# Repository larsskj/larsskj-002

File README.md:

An Arduino shield for connecting TLC 5940 boards
================================================

### larsskj-002

This project is an Arduino shield created in KiCAD to connect one or more TLC 5940 LED controllers using ordinary IDC connectors and flat cable.

The board is shared at [OSH Park](https://oshpark.com/shared_projects/Qwm4SQ2z), where you can order copies.

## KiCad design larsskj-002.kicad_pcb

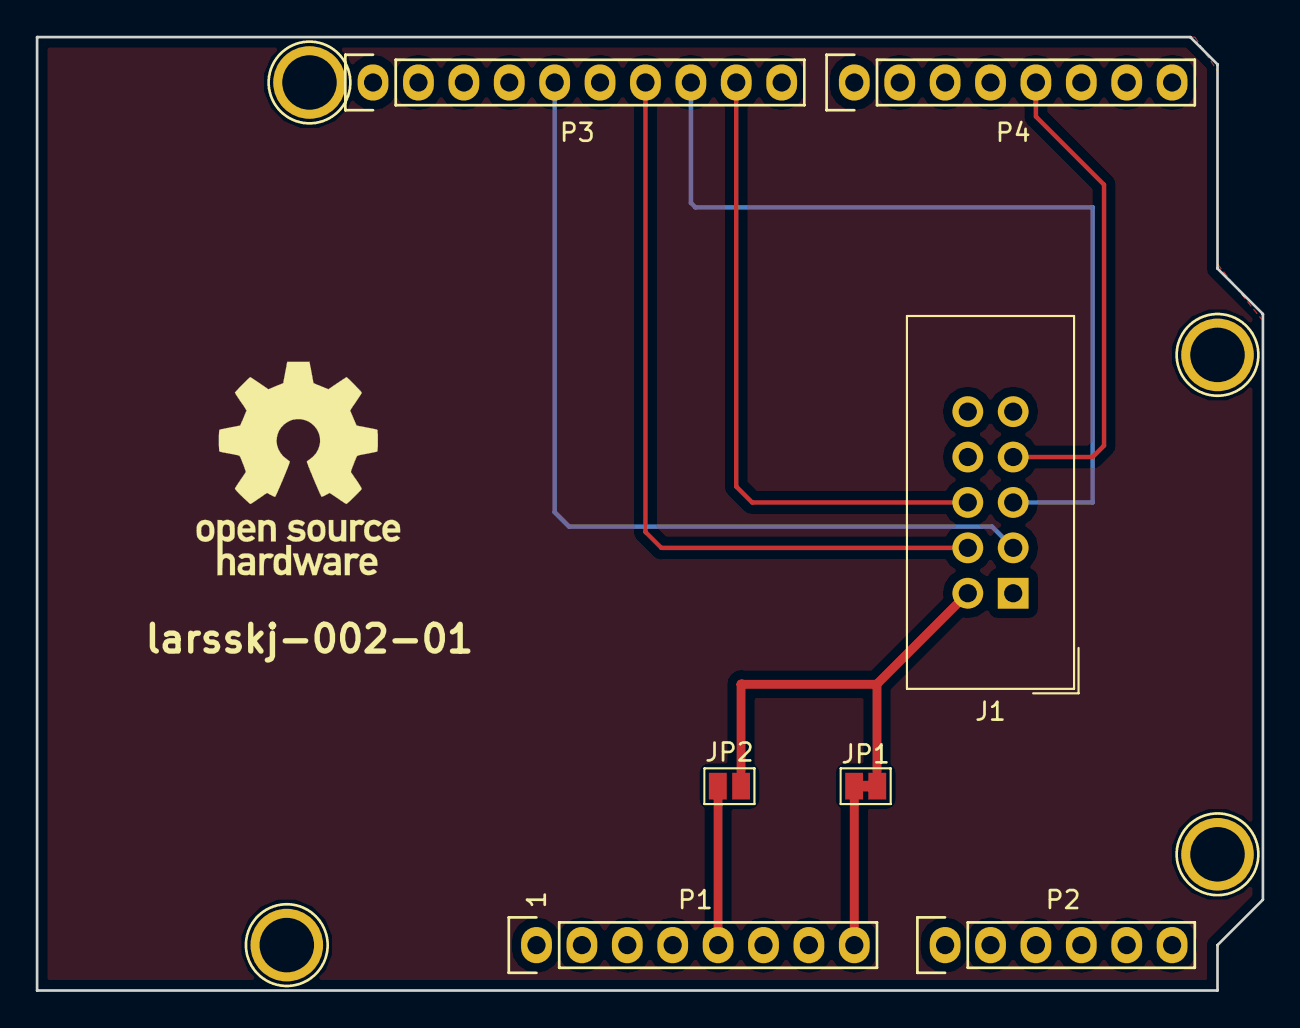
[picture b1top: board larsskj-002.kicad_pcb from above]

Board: 2 copper layers, 68.6 x 53.3 mm, 11 parts (0 on the bottom side), 11 nets.

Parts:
J1: TLC; IDC-Header_2x05_P2.54mm_Vertical
JP1: Jumper_NC_Small; SolderJumper-2_P1.3mm_Bridged_Pad1.0x1.5mm
JP2: Jumper_NO_Small; SolderJumper-2_P1.3mm_Open_Pad1.0x1.5mm
P1: Power; Socket_Strip_Arduino_1x08
P2: Analog; Socket_Strip_Arduino_1x06
P3: Digital; Socket_Strip_Arduino_1x10
P4: Digital; Socket_Strip_Arduino_1x08
P5, P6, P7, P8: CONN_01X01; Arduino_1pin

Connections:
+5V: JP2.2, P1.5
/3(**): J1.7, P4.5
/9(**): J1.6, P3.9
/10(**/SS): J1.5, P3.8
/11(**/MOSI): J1.4, P3.7
/13(SCK): J1.3, P3.5
/A4: P2.5, P3.2
/A5: P2.6, P3.1
/Vin: JP1.1, P1.8
GND: J1.1, J1.9, P1.6, P1.7, P3.4
unnamed: J1.2, JP1.2, JP2.1

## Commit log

2019-03-30 Initial import
2019-04-12 .gitignore added
